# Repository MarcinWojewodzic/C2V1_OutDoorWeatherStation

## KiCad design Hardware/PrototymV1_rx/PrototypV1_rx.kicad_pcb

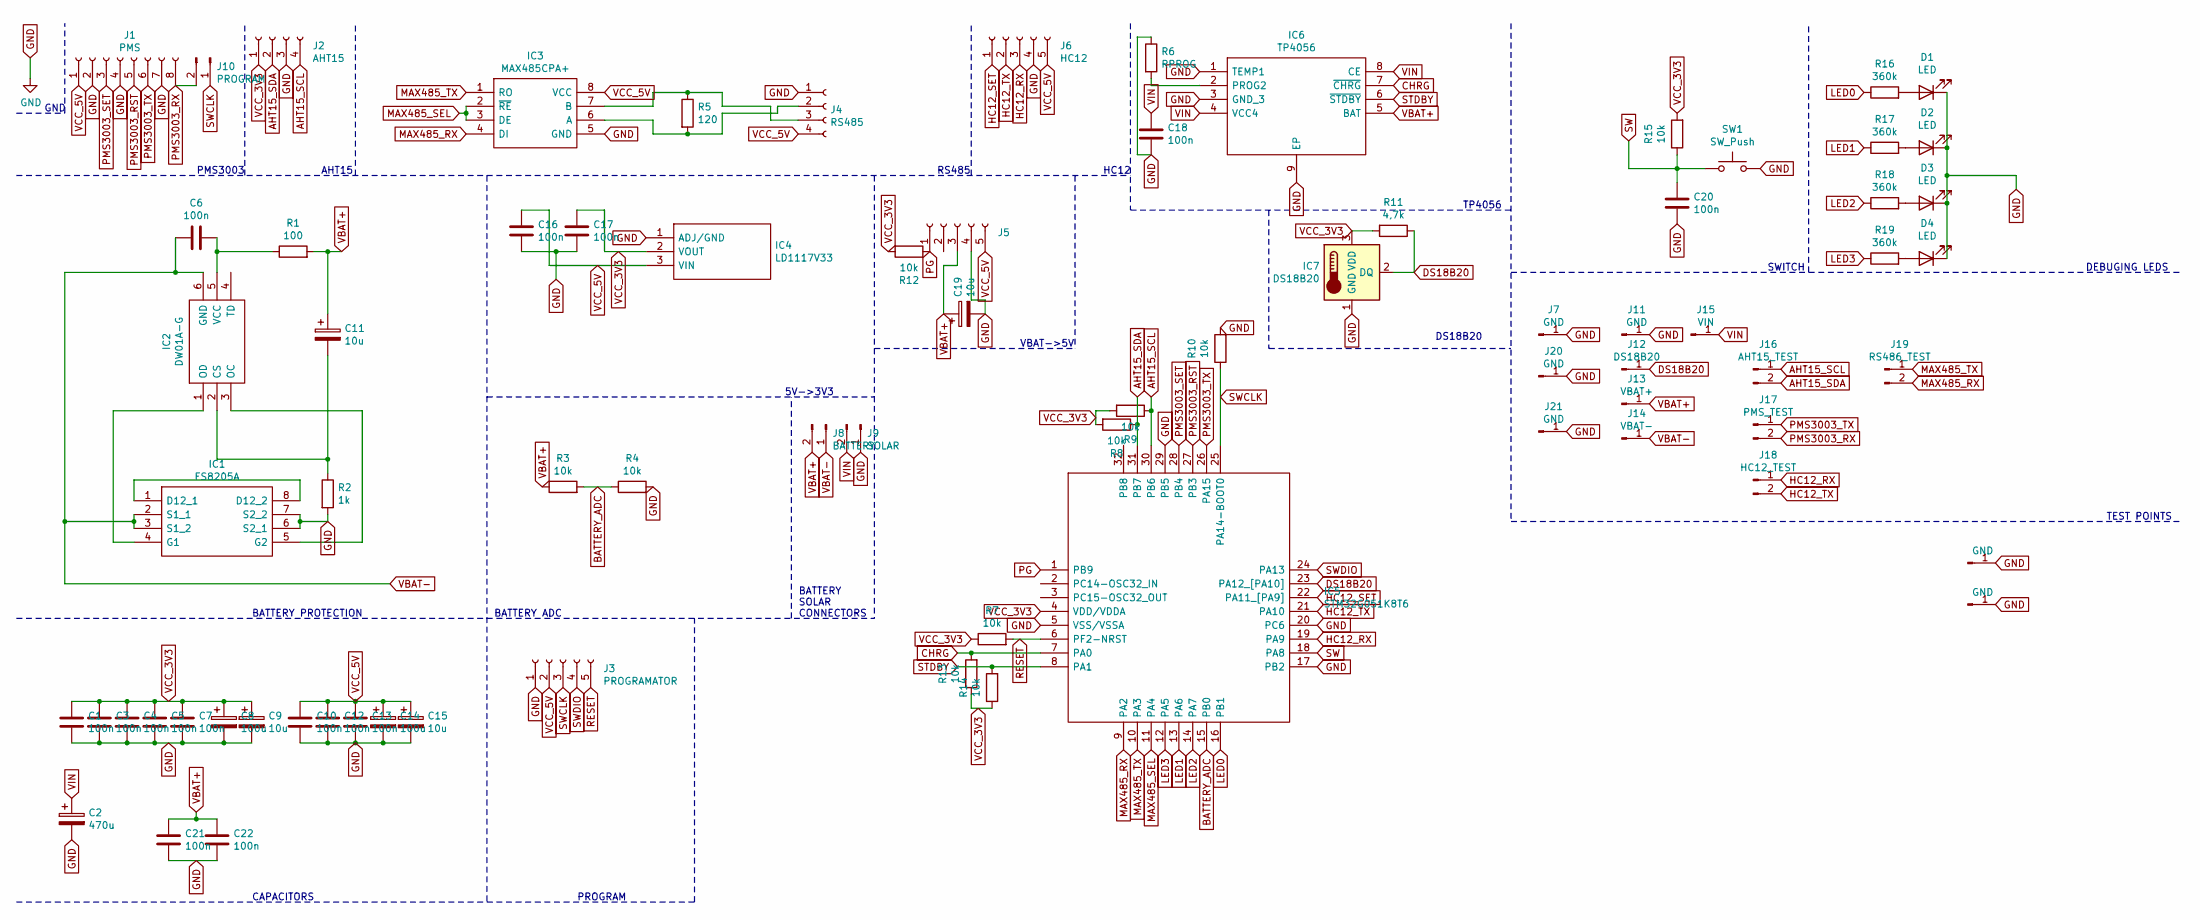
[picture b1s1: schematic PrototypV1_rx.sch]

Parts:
C1, C3, C4, C5, C6, C7, C10, C12, C13, C16, C17, C18, C20, C21, C22: 100n; C_1206_3216Metric_Pad1.33x1.80mm_HandSolder
C2: 470u; CP_Elec_8x10.5
C8, C14: 100u; CP_Elec_5x5.4
C9, C11, C15, C19: 10u; CP_Elec_4x5.4
D1, D2, D3, D4: LED; D_1206_3216Metric_Pad1.42x1.75mm_HandSolder
IC1: FS8205A; SOP65P640X120-8N; Manufacturer_Part_Number FS8205A
IC2: DW01A-G; SOT95P190X145-6N; Manufacturer_Part_Number DW01A-G
IC3: MAX485CPA+; DIP794W56P254L938H457Q8N; Manufacturer_Part_Number MAX485CPA+; Mouser Part Number 700-MAX485CPA
IC4: LD1117V33; TO255P460X1020X2008-3P; Manufacturer_Part_Number LD1117V33; Mouser Part Number 511-LD1117V33
IC5: STM32G051K8T6; QFP80P900X900X160-32N; Manufacturer_Part_Number STM32G051K8T6; Mouser Part Number 511-STM32G051K8T6
IC6: TP4056; SOIC127P600X175-9N; Manufacturer_Part_Number TP4056
IC7: DS18B20; TO-92_Inline
J1: PMS; PinHeader_1x08_P2.54mm_Vertical
J2: AHT15; PinHeader_1x04_P1.27mm_Horizontal
J3: PROGRAMATOR; PinHeader_1x05_P2.54mm_Vertical
J4: RS485; TerminalBlock_bornier-4_P5.08mm
J5: PinHeader_1x05_P2.54mm_Vertical
J6: HC12; PinHeader_1x05_P2.54mm_Vertical
J7, J11, J20, J21, J23: GND; PinHeader_1x01_P2.54mm_Vertical
J8: BATTERY; PinHeader_1x02_P2.54mm_Vertical
J9: SOLAR; PinHeader_1x02_P2.54mm_Vertical
J10: PROGRAM; PinHeader_1x02_P2.54mm_Vertical
J12: DS18B20; PinHeader_1x01_P2.54mm_Vertical
J13: VBAT+; PinHeader_1x01_P2.54mm_Vertical
J14: VBAT-; PinHeader_1x01_P2.54mm_Vertical
J15: VIN; PinHeader_1x01_P2.54mm_Vertical
J16: AHT15_TEST; PinHeader_1x02_P2.54mm_Vertical
J17: PMS_TEST; PinHeader_1x02_P2.54mm_Vertical
J18: HC12_TEST; PinHeader_1x02_P2.54mm_Vertical
J19: RS486_TEST; PinHeader_1x02_P2.54mm_Vertical
R1: 100; R_1206_3216Metric_Pad1.30x1.75mm_HandSolder
R2: 1k; R_1206_3216Metric_Pad1.30x1.75mm_HandSolder
R3, R4, R7, R8, R9, R10, R12, R13, R14, R15: 10k; R_1206_3216Metric_Pad1.30x1.75mm_HandSolder
R5: 120; R_1206_3216Metric_Pad1.30x1.75mm_HandSolder
R6: RPROG; R_Axial_DIN0309_L9.0mm_D3.2mm_P15.24mm_Horizontal
R11: 4,7k; R_1206_3216Metric_Pad1.30x1.75mm_HandSolder
R16, R17, R18, R19: 360k; R_1206_3216Metric_Pad1.30x1.75mm_HandSolder
SW1: SW_Push; SW_Push_1P1T_NO_6x6mm_H9.5mm
ghj1: GND; PinHeader_1x01_P2.54mm_Vertical

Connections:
AHT15_SCL: IC5.30 (PB6), J2.4, J16.1, R9.1
AHT15_SDA: IC5.31 (PB7), J2.2, J16.2, R8.1
BATTERY_ADC: IC5.15 (PB0), R3.2, R4.1
CHRG: IC5.7 (PA0), IC6.7 (~CHRG), R13.2
DS18B20: IC5.23 (PA12_[PA10]), IC7.2 (DQ), J12.1, R11.1
GND: C1.2, C2.2, C3.2, C4.2, C5.2, C7.2, C8.2, C9.2, C10.2, C12.2, C13.2, C14.2, C15.2, C16.2, C17.2, C18.2, C19.2, C20.2, C21.2, C22.2, D1.1 (K), D2.1 (K), D3.1 (K), D4.1 (K), IC1.6 (S2_1), IC1.7 (S2_2), IC3.5 (GND), IC4.1 (ADJ/GND), IC5.5 (VSS/VSSA), IC5.17 (PB2), IC5.20 (PC6), IC5.29 (PB5), IC6.1 (TEMP1), IC6.3 (GND_3), IC6.9 (EP), IC7.1 (GND), J1.2, J1.4, J1.7, J2.3, J3.1, J4.1, J5.4, J6.4, J7.1, J9.1, J11.1, J20.1, J21.1, J23.1, R2.2, R4.2, R6.1, R10.2, SW1.2, ghj1.1
HC12_RX: IC5.19 (PA9), J6.3, J18.1
HC12_SET: IC5.22 (PA11_[PA9]), J6.1
HC12_TX: IC5.21 (PA10), J6.2, J18.2
LED0: IC5.16 (PB1), R16.1
LED1: IC5.13 (PA6), R17.1
LED2: IC5.14 (PA7), R18.1
LED3: IC5.12 (PA5), R19.1
MAX485_RX: IC3.4 (DI), IC5.9 (PA2), J19.2
MAX485_SEL: IC3.2 (~RE), IC3.3 (DE), IC5.11 (PA4)
MAX485_TX: IC3.1 (RO), IC5.10 (PA3), J19.1
unnamed: C6.2, IC2.5 (VCC), R1.1
unnamed: C11.2, IC2.2 (CS), R2.1
unnamed: D1.2 (A), R16.2
unnamed: D2.2 (A), R17.2
unnamed: D3.2 (A), R18.2
unnamed: D4.2 (A), R19.2
unnamed: IC1.1 (D12_1), IC1.8 (D12_2)
unnamed: IC1.4 (G1), IC2.1 (OD)
unnamed: IC1.5 (G2), IC2.3 (OC)
unnamed: IC3.6 (A), J4.2, R5.2
unnamed: IC3.7 (B), J4.3, R5.1
unnamed: IC6.2 (PROG2), R6.2
PG: IC5.1 (PB9), J5.1, R12.1
PMS3003_RST: IC5.27 (PB3), J1.5
PMS3003_RX: J1.8, J10.2, J17.2
PMS3003_SET: IC5.28 (PB4), J1.3
PMS3003_TX: IC5.26 (PA15), J1.6, J17.1
RESET: IC5.6 (PF2-NRST), J3.5, R7.2
STDBY: IC5.8 (PA1), IC6.6 (~STDBY), R14.2
SW: C20.1, IC5.18 (PA8), R15.1, SW1.1
SWCLK: IC5.25 (PA14-BOOT0), J3.3, J10.1, R10.1
SWDIO: IC5.24 (PA13), J3.4
VBAT+: C11.1, C19.1, C21.1, C22.1, IC6.5 (BAT), J5.3, J8.2, J13.1, R1.2, R3.1
VBAT-: C6.1, IC1.2 (S1_1), IC1.3 (S1_2), IC2.6 (GND), J8.1, J14.1
VCC_3V3: C1.1, C3.1, C4.1, C5.1, C7.1, C8.1, C9.1, C17.1, IC4.2 (VOUT), IC5.4 (VDD/VDDA), IC7.3 (VDD), J2.1, R7.1, R8.2, R9.2, R11.2, R12.2, R13.1, R14.1, R15.2
VCC_5V: C10.1, C12.1, C13.1, C14.1, C15.1, C16.1, IC3.8 (VCC), IC4.3 (VIN), J1.1, J3.2, J4.4, J5.5, J6.5
VIN: C2.1, C18.1, IC6.4 (VCC4), IC6.8 (CE), J9.2, J15.1

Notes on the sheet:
GND
PMS3003
AHT15
RS485
HC12
TP4056
BATTERY PROTECTION
5V->3V3
VBAT->5V
BATTERY ADC
CAPACITORS
PROGRAM
DS18B20
BATTERY SOLAR CONNECTORS
SWITCH
DEBUGING LEDS
TEST POINTS

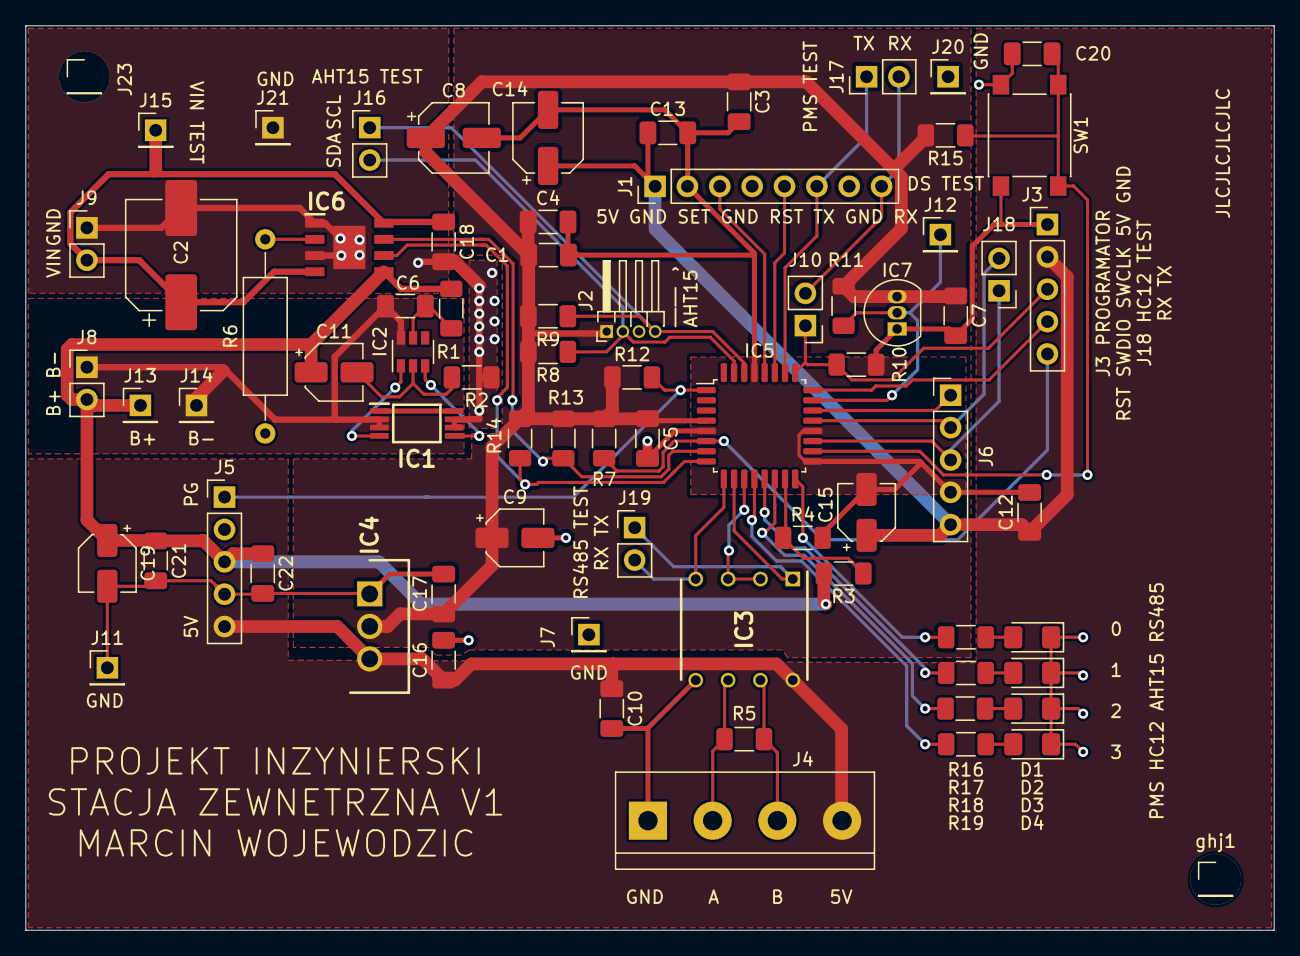
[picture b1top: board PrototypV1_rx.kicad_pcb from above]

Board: 2 copper layers, 98.0 x 71.0 mm, 76 parts (0 on the bottom side), 43 nets.

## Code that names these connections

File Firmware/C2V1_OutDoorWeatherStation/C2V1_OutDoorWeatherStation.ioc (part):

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Mcu.Name=STM32G051K(6-8)Tx
Mcu.Package=LQFP32
Mcu.UserName=STM32G051K8Tx
PA0.GPIOParameters=GPIO_Label
PA0.GPIO_Label=BATTERY_CHRG
PA0.Signal=GPIO_Input
PA1.GPIOParameters=GPIO_Label
PA1.GPIO_Label=BATTERY_STDBY
PA1.Signal=GPIO_Input
PA10.Mode=Asynchronous
PA10.Signal=USART1_RX
PA11\ [PA9].GPIOParameters=PinState,GPIO_Label
PA11\ [PA9].GPIO_Label=HC12_SET
PA11\ [PA9].PinState=GPIO_PIN_SET
PA11\ [PA9].Signal=GPIO_Output
PA12\ [PA10].GPIOParameters=GPIO_Speed,GPIO_Label
PA12\ [PA10].GPIO_Label=DS18B20
PA12\ [PA10].GPIO_Speed=GPIO_SPEED_FREQ_VERY_HIGH
PA12\ [PA10].Signal=GPIO_Output
PA14-BOOT0.Mode=Asynchronous
PA14-BOOT0.Signal=USART2_TX
PA15.Mode=Asynchronous
PA15.Signal=USART2_RX
PA2.Mode=Asynchronous
PA2.Signal=LPUART1_TX
PA3.Mode=Asynchronous
PA3.Signal=LPUART1_RX
PA4.GPIOParameters=GPIO_Label
PA4.GPIO_Label=MAX485_SEL
PA4.Signal=GPIO_Output
PA5.GPIOParameters=GPIO_Label
PA5.GPIO_Label=LED3
PA5.Signal=GPIO_Output
PA6.GPIOParameters=GPIO_Label
PA6.GPIO_Label=LED1
PA6.Signal=GPIO_Output
PA7.GPIOParameters=GPIO_Label
PA7.GPIO_Label=LED2
PA7.Signal=GPIO_Output
PA8.GPIOParameters=GPIO_Label,GPIO_ModeDefaultEXTI
PA8.GPIO_Label=SWITCH
PA8.GPIO_ModeDefaultEXTI=GPIO_MODE_IT_FALLING
PA8.Signal=GPXTI8
PA9.Mode=Asynchronous
PA9.Signal=USART1_TX
PB0.Mode=IN8
PB0.Signal=ADC1_IN8
PB1.GPIOParameters=GPIO_Label
PB1.GPIO_Label=LED0
PB1.Signal=GPIO_Output
PB3.GPIOParameters=PinState,GPIO_Label
PB3.GPIO_Label=PMS_RST
PB3.PinState=GPIO_PIN_SET
PB3.Signal=GPIO_Output
PB4.GPIOParameters=GPIO_Label
PB4.GPIO_Label=PMS_SET
PB4.Signal=GPIO_Output
PB6.GPIOParameters=GPIO_Speed
PB6.GPIO_Speed=GPIO_SPEED_FREQ_VERY_HIGH
PB6.Mode=I2C
PB6.Signal=I2C1_SCL
PB7.GPIOParameters=GPIO_Speed
PB7.GPIO_Speed=GPIO_SPEED_FREQ_VERY_HIGH
PB7.Mode=I2C
PB7.Signal=I2C1_SDA
PB9.GPIOParameters=GPIO_Label
PB9.GPIO_Label=COVERTER_PG
PB9.Signal=GPIO_Input
RCC.HSE_VALUE=8000000
RCC.SYSCLKFreq_VALUE=16000000
board=custom

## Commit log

2022-09-23 Dodano ClangFormat
2022-10-08 rozpoczęcie
2022-10-09 Wszystkie protokoły działają i dodano prototyp Sm
2022-10-09 Prototyp Sm dla Switch
2022-10-22 Dodano podstawowe RFP
2022-10-29 Dodano bibliotekę do AHT15
2022-10-29 Dodano biblioteki do czujników
2022-11-05 Dodano łączność z C1V1
2022-11-06 Powoli do brzegu z tym projektem
2022-11-18 Dodana bateria i PMS
2023-01-15 Ukończono
